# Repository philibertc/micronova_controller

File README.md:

# micronova_controller  

**Kits are available on Tindie!**  
**_In stock every month._**  

**Here is an overview of the additions:**

- **possibility to reset the settings with a flat screwdriver**
- **IO footprints are now designed to accept screw terminals**
- **D0 and RST are connected for deep sleep**
- **a row of pins has been added to access unused pins**

This Arduino program allows to control easily via MQTT a pellet stove equipped with a Micronova mainboard. Hardware details [here.](https://github.com/philibertc/micronova_controller_pcb/)  
**Discord server: https://github.com/philibertc/micronova_controller/discussions/63**

## License
<br />This work is licensed under a <a rel="license" href="http://creativecommons.org/licenses/by-nc-sa/4.0/">Creative Commons Attribution-NonCommercial-ShareAlike 4.0 International License</a>.
All previous commits [from this one (3 sept 2022)](https://github.com/philibertc/micronova_controller/commit/3b48e56f5a7b02a50885eb272f03c7dd73d8c4e8) are CC-BY-NC-ND and not CC-BY-NC-SA.

## Please check the [Wiki](https://github.com/philibertc/micronova_controller/wiki)

## Thanks
Thanks to [@pedrware](https://github.com/pedrware) for the photo of the mainboard and his explanations of some of the problems encountered.  
Thanks to [ridiculouslab](https://www.ridiculouslab.com/arguments/iot/stufa/micronova_en.php) for his analysis of the serial protocol.  
Thanks to the active Discord community, who keep the project moving.  
Thanks to [PCBWay](https://www.pcbway.com/) for supporting me in the production of PCBs.

## Disclaimer
THIS SOFTWARE IS PROVIDED "AS IS" AND ANY EXPRESSED OR IMPLIED WARRANTIES, INCLUDING, BUT NOT LIMITED TO, THE IMPLIED WARRANTIES OF MERCHANTABILITY AND FITNESS FOR A PARTICULAR PURPOSE ARE DISCLAIMED. IN NO EVENT SHALL THE REGENTS OR CONTRIBUTORS BE LIABLE FOR ANY DIRECT, INDIRECT, INCIDENTAL, SPECIAL, EXEMPLARY, OR CONSEQUENTIAL DAMAGES (INCLUDING, BUT NOT LIMITED TO, PROCUREMENT OF SUBSTITUTE GOODS OR SERVICES; LOSS OF USE, DATA, OR PROFITS; OR BUSINESS INTERRUPTION)
HOWEVER CAUSED AND ON ANY THEORY OF LIABILITY, WHETHER IN CONTRACT, STRICT LIABILITY, OR TORT (INCLUDING NEGLIGENCE OR OTHERWISE) ARISING IN ANY WAY OUT OF THE USE OF THIS SOFTWARE, EVEN IF ADVISED OF THE POSSIBILITY OF SUCH DAMAGE.

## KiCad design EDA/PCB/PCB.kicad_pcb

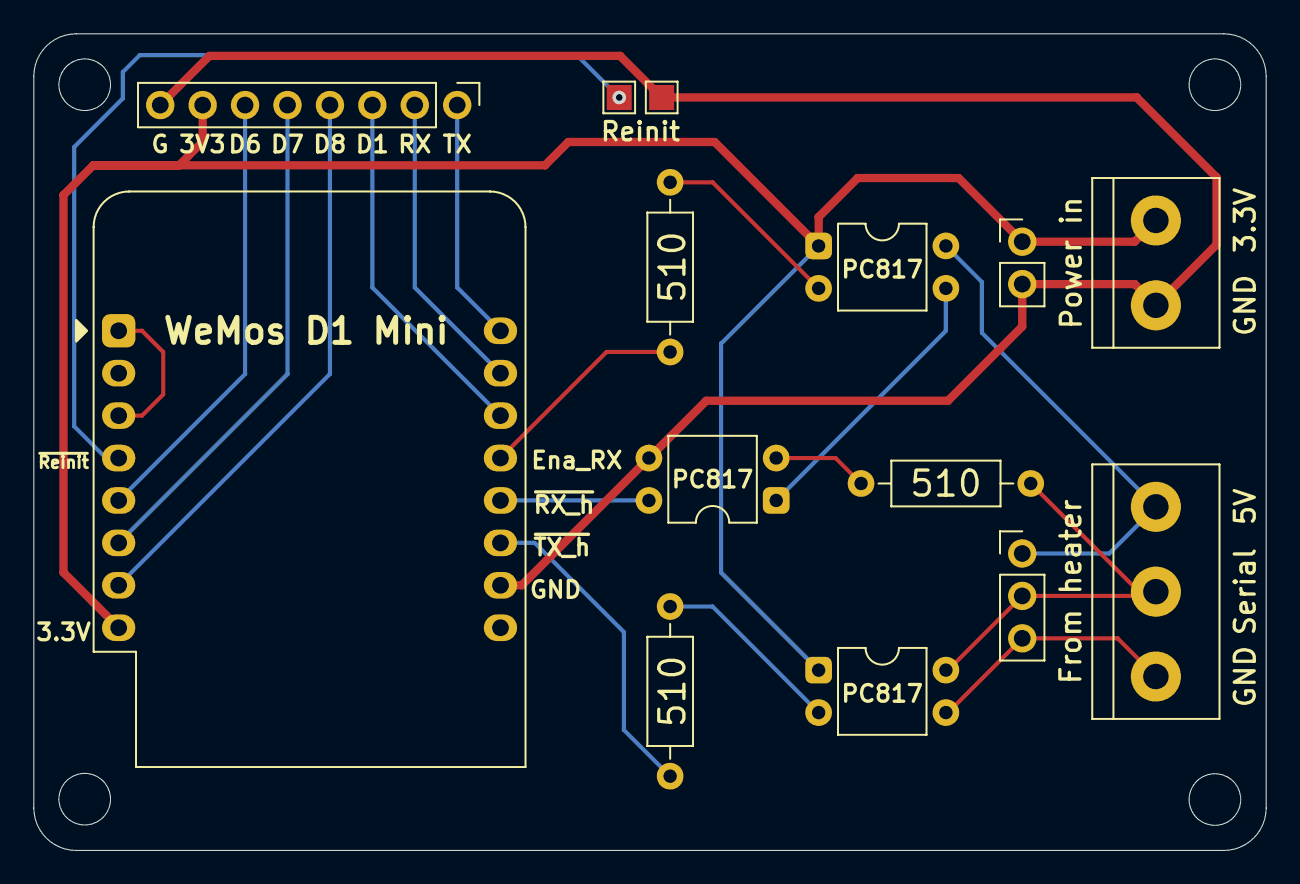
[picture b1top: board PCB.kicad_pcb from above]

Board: 2 copper layers, 73.8 x 48.9 mm, 14 parts (0 on the bottom side), 20 nets.

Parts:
J1: Conn_01x08_Female; PinHeader_1x08_P2.54mm_Vertical
J2: Screw_Terminal_01x02; TerminalBlock_bornier-2_P5.08mm
J3: Screw_Terminal_01x03; TerminalBlock_bornier-3_P5.08mm
J4: Conn_01x02_Male; PinHeader_1x02_P2.54mm_Vertical
J5: Conn_01x03_Male; PinHeader_1x03_P2.54mm_Vertical
R1, R2, R3: 500; R_Axial_DIN0207_L6.3mm_D2.5mm_P10.16mm_Horizontal
TP1, TP2: TestPoint_Flag; TestPoint_Pad_1.5x1.5mm
U1, U2, U4: PC817; DIP-4_W7.62mm
U3: WeMos D1 Mini; WEMOS_D1_mini_light

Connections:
unnamed: J1.1, U3.16
unnamed: J1.2, U3.15
unnamed: J1.3, U3.14
unnamed: J1.4, U3.7
unnamed: J1.5, U3.6
unnamed: J1.6, U3.5
unnamed: J1.7, J2.1, J4.1, U1.1, U3.8, U4.1
unnamed: J1.8, J2.2, J4.2, TP2.1, U2.3, U3.10
unnamed: J3.1, J5.1, U1.4
unnamed: J3.2, J5.2, R2.1, U4.4
unnamed: J3.3, J5.3, U4.3
unnamed: R1.1, U1.2
unnamed: R1.2, U3.13
unnamed: R2.2, U2.2
unnamed: R3.1, U4.2
unnamed: R3.2, U3.11
unnamed: TP1.1, U3.4
unnamed: U1.3, U2.1
unnamed: U2.4, U3.12
unnamed: U3.1, U3.3

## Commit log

2021-07-11 First version of the code
2021-07-11 Correcting some errors
2021-07-11 Enhancement
2021-07-19 Edit micronova_controller.ino
2021-07-25 Added debugging tests
2021-07-27 WiFiManagerParameter try
2021-07-30 Set up WiFiManager to display MQTT settings
2021-08-02 WiFiManager parameters work
2021-08-07 Correcting errors
    Tests are working.
2021-08-08 Update main code
2021-08-09 PubSubClient errors
2021-08-10 It's working
2021-08-10 Reset function
2021-08-10 ESP32
2021-08-10 Get states every 10 sec
2021-08-10 Remove char_mqtt_topic
2021-08-10 Clarifications
2021-08-11 Comments
2021-08-14 Update PCB
2021-08-14 Better arrangement of the traces
2021-08-14 500R to 510R
2021-08-14 Add gerber files
2021-08-14 Gerber
2021-09-03 Non important PCB changes
2021-09-03 Regenerating gerber
2021-09-05 Smaller PCB
2021-09-05 Flame power 0 = 0FF
2021-09-06 Fume temp test
2021-09-06 Some tests
2021-09-11 Update program
2021-09-11 Correting errors
2021-09-11 Update doc
2021-09-12 Fume temp
2021-09-12 Prepare for new features
2021-09-22 New values readings
2021-09-23 Check state every 25 sec
2021-09-25 Removing buggy new features Will be reimplemented after debug.
2021-09-25 New features and corrections
2021-09-25 Returning to a fully working program
2021-09-26 Stable state
2021-10-02 Water pressure in bar
2021-10-03 Pong "Powered up" is sent every 25s on mqtt_topic/pong
2021-10-03 Correcting errors in comments
2021-10-05 Correcting errors
2021-10-05 forceOff
2021-10-16 Preparing for new feature You will soon be able to put the ESP in deep sleep and wake it up remotely.
2021-10-18 PCB v2
    Soon on Tindie (if there are enough people interested)
    https://github.com/philibertc/micronova_controller/discussions/17#discussioncomment-1496990
2021-10-18 Update PCB's legends
2021-10-20 Removal of obsolete Gerber files
2021-10-24 Create dev branch
2021-10-24 Final Gerber
    Files used for the "v2" version sold on Tindie.
2021-10-25 Solve float errors
2021-10-31 Create PCB.kicad_pcb-rounded
2021-11-01 Set theme jekyll-theme-cayman
2021-11-03 Some enhancements
2021-11-07 Fixes in test prog
2021-12-04 waterSet
2021-12-12 Revert waterSet commit
2022-02-25 Update micronova_controller.ino
    Add OTA
2022-03-05 Adding OTA and cleaning This version isn't tested yet so please use the previous one
2022-03-06 OTA Please use commit 6b27eb0
2022-03-06 Correcting comments Please use commit 6b27eb0
2022-03-06 Correcting duplicated reconnect() Please use commit 6b27eb0
2022-03-06 New version working! But more tests are needed for the OTA
2022-09-03 CC-BY-NC-ND to CC-BY-NC-SA
2022-10-29 fix: variable waterset is wrong
2022-10-29 feat: update documentation to include Solius Geres
    - https://solius.pt/pt/view/pdf/Solius_Hidroline_manual_utilizacao.pdf
2022-10-31 feat: adds AutoDiscover sensors for HomeAssistant
2022-11-08 Writing / reading ALL values (EEPROM/RAM)
    Some additions out of brain as I still remember them, full source code for writing / reading values left on other computor.
    Gimme 2 days
2022-11-13 Update to read / write temps & stove power
    Dirty values code - but works like a charm on Feretti stove.
    For reading EEPROM values we must add 0x20 to the address - the stove replies with added value (e.g. 0x7F becomes 0x9F in RX from stove, we still write to 0x7F)
    TODO: calculate checksum automagically, if checskum is higher than 0xFF then we must substract 256Dec from value - now we MUST know if the value will be higher than 0xFF and calculate accordingly.
    Confirm working for ~7 days with HomeAssistant.
2022-12-30 Add new Model "L'Asolana Marina"
    Hey, as promised in #53, here my MR:
    This model has no boiler at all. I figured out a few more options to control, see here: https://github.com/eni23/micronova-controller#known-locations but the ones you use for temp, fumes, fan and tur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
2023-02-17 Add new model and brand "Palladio Olanda"
    Added new brand: Palladio
    And added new model "Palladio Olanda", it all works
2023-02-18 Update micronova_controller.ino
    Changed the º symbol, that is the masculine ordinal indicator to the correct ° degree symbol.
2023-02-26 Creating files
2025-11-05 Enhance PCBWay info
    Updated PayPal donation link and improved PCBWay description.
2026-05-14 Adding Lectronz badge

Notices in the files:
EDA/PCB/PCB.kicad_pcb:
License: CC-BY-NC-ND
